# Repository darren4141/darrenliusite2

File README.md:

https://darren4141.github.io/darrenliusite2/

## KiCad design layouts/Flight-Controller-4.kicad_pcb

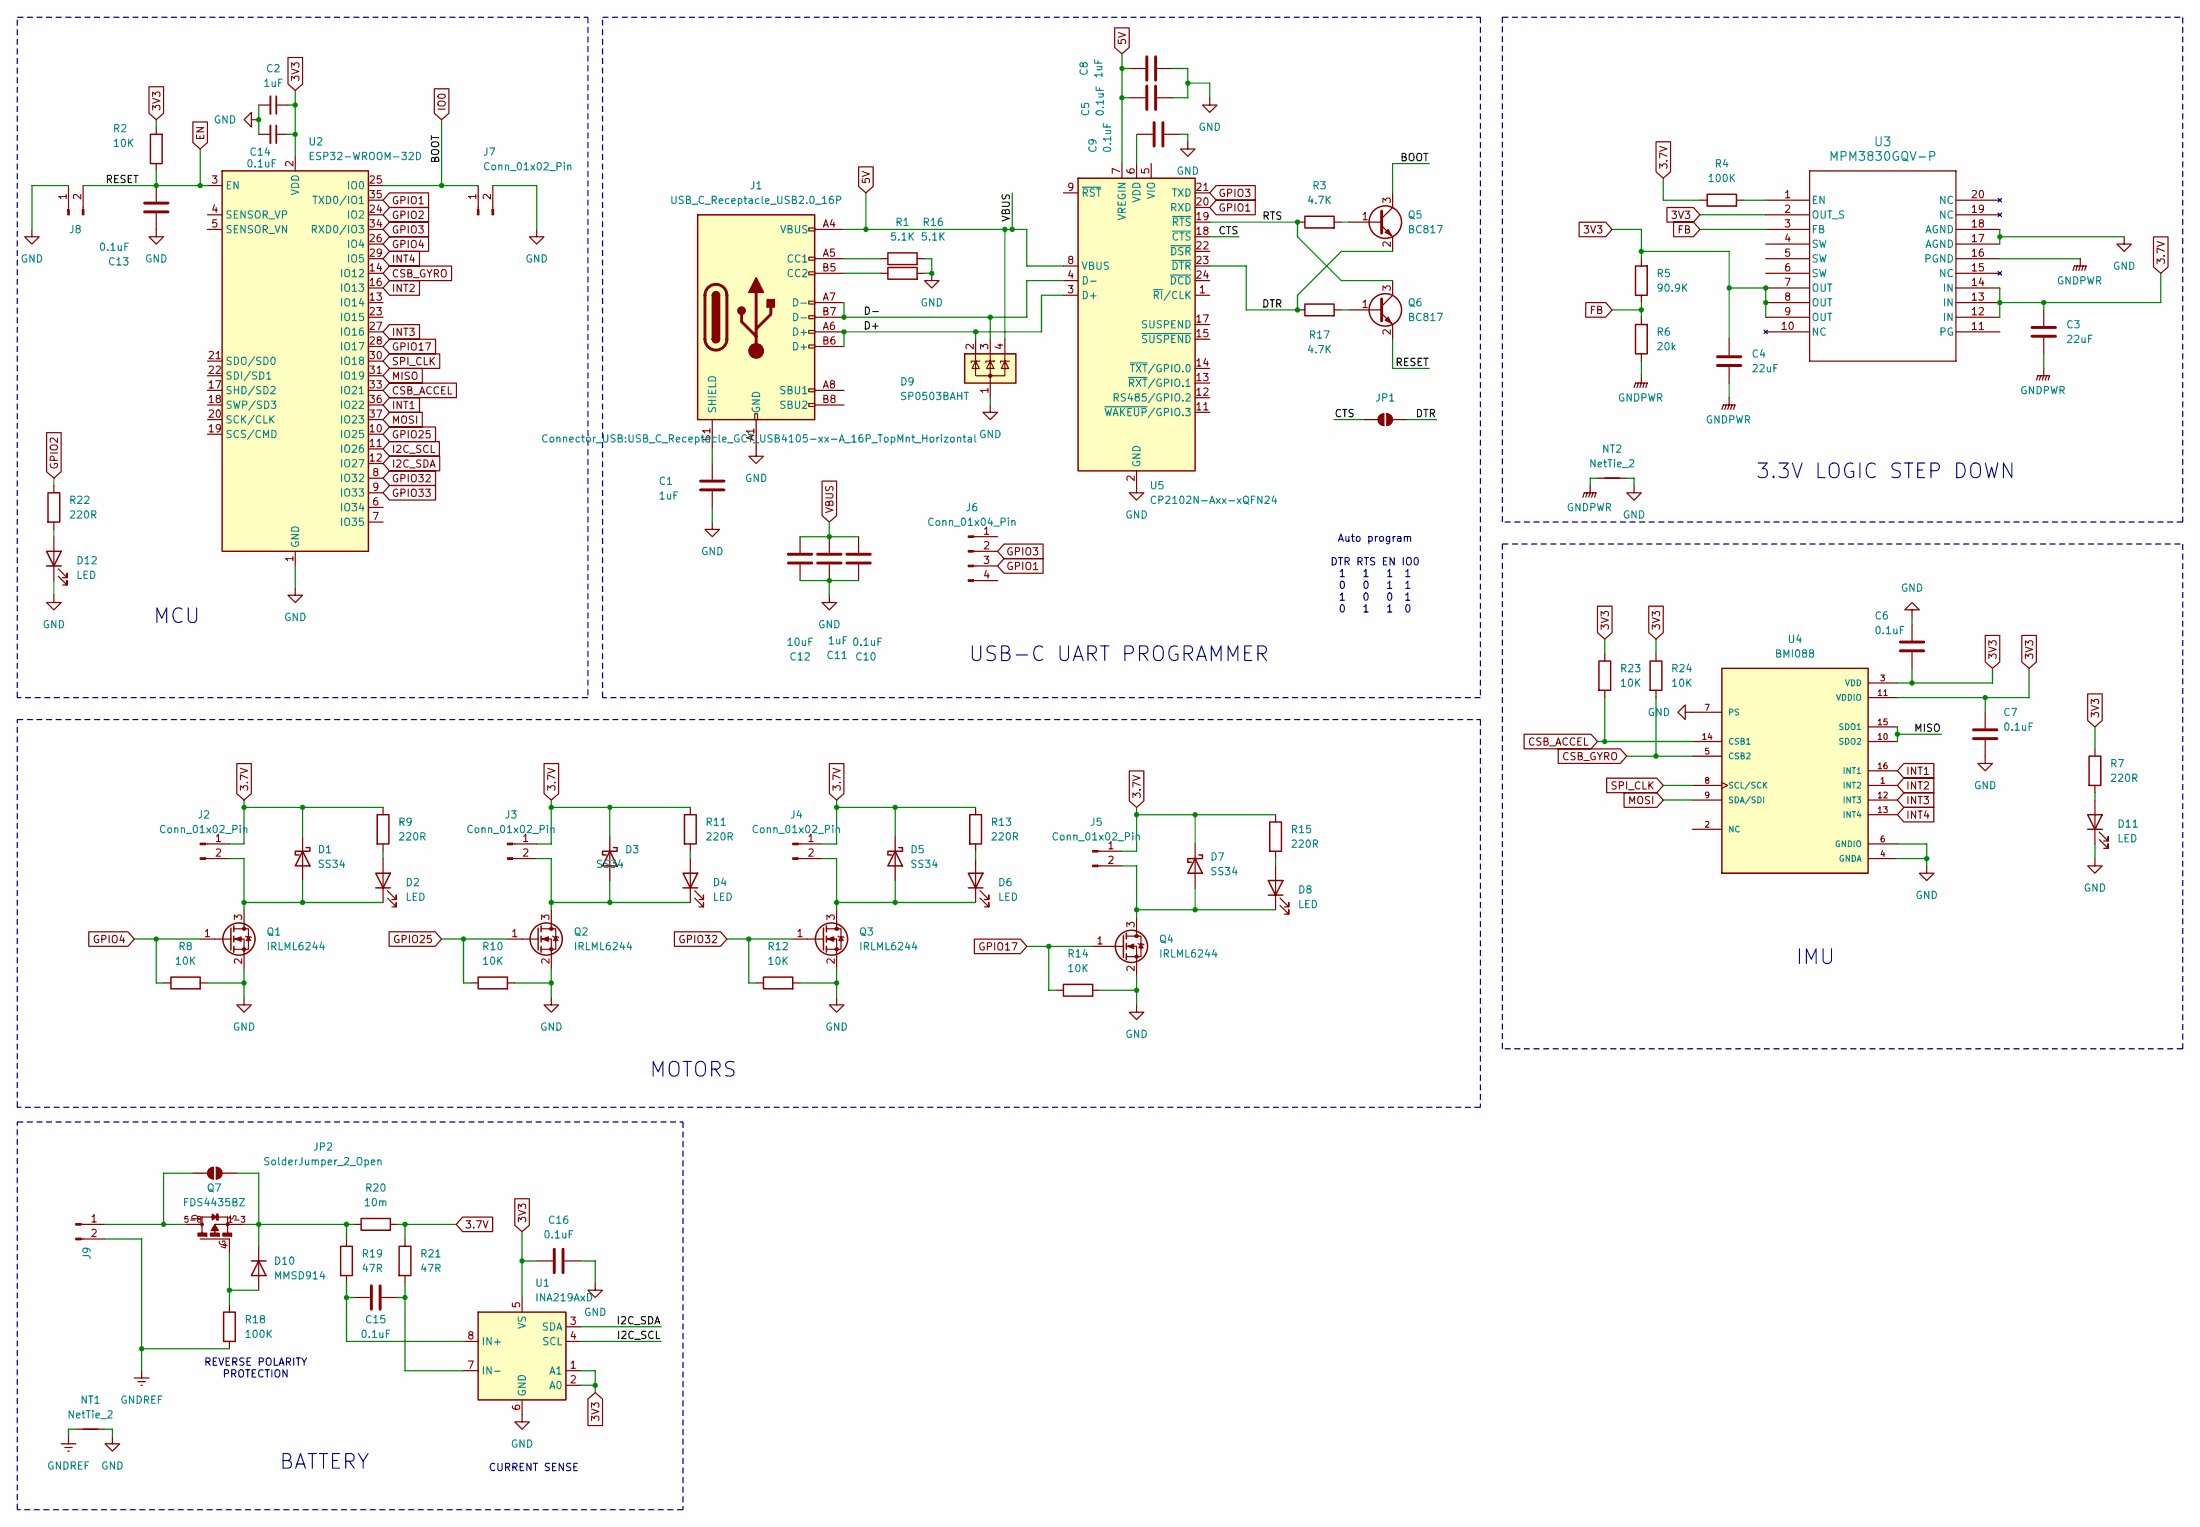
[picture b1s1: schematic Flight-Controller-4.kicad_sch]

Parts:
C1, C2, C8, C11: 1uF; C_0603_1608Metric
C3, C4: 22uF; C_1210_3225Metric
C5, C6, C7, C9, C10, C13, C14, C15, C16: 0.1uF; C_0603_1608Metric
C12: 10uF; C_0603_1608Metric
D1, D3, D5, D7: SS34; D_SMA
D2, D4, D6, D8, D11, D12: LED; LED_0603_1608Metric
D9: SP0503BAHT; SOT-143
D10: MMSD914; D_SOD-123
J1: USB_C_Receptacle_USB2.0_16P; USB_C_Receptacle_GCT_USB4105-xx-A_16P_TopMnt_Horizontal
J2, J3, J4, J5: Conn_01x02_Pin; Hirose_DF13-02P-1.25DSA_1x02_P1.25mm_Vertical
J6: Conn_01x04_Pin; PinHeader_1x04_P2.54mm_Vertical
J7, J8: Conn_01x02_Pin; PinHeader_1x02_P2.54mm_Vertical
J9: Conn_01x02_Pin; JST_XH_S2B-XH-A-1_1x02_P2.50mm_Horizontal
JP1: SolderJumper_2_Open; SolderJumper-2_P1.3mm_Open_RoundedPad1.0x1.5mm
JP2: SolderJumper_2_Open; SolderJumper-2_P1.3mm_Open_Pad1.0x1.5mm
NT1, NT2: NetTie_2; NetTie-2_SMD_Pad0.5mm
Q1, Q2, Q3, Q4: IRLML6244; SOT-23
Q5, Q6: BC817; SOT-23
Q7: FDS4435BZ; SO08-E3
R1, R16: 5.1K; R_0603_1608Metric
R2, R8, R10, R12, R14, R23, R24: 10K; R_0603_1608Metric
R3, R17: 4.7K; R_0603_1608Metric
R4, R18: 100K; R_0603_1608Metric
R5: 90.9K; R_0603_1608Metric
R6: 20k; R_0603_1608Metric
R7, R9, R11, R13, R15, R22: 220R; R_0603_1608Metric
R19, R21: 47R; R_0603_1608Metric
R20: 10m; R_0805_2012Metric
U1: INA219AxD; SOIC-8_3.9x4.9mm_P1.27mm
U2: ESP32-WROOM-32D
U3: MPM3830GQV-P; QFN3p0x5p0x1p6_MPM3830_MNP
U4: BMI088; PQFN50P450X300X100-16N
U5: CP2102N-Axx-xQFN24; QFN-24-1EP_4x4mm_P0.5mm_EP2.5x2.5mm

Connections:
3.7V: C3.1, D1.1 (K), D3.1 (K), D5.1 (K), D7.1 (K), J2.1, J3.1, J4.1, J5.1, R4.1, R9.1, R11.1, R13.1, R15.1, R20.2, R21.1, U3.12 (IN), U3.13 (IN), U3.14 (IN)
3V3: C2.1, C4.1, C6.2, C7.1, C14.1, C16.1, R2.2, R5.2, R7.1, R23.1, R24.1, U1.1 (A1), U1.2 (A0), U1.5 (VS), U2.2 (VDD), U3.2 (OUT_S), U3.7 (OUT), U3.8 (OUT), U3.9 (OUT), U4.3 (VDD), U4.11 (VDDIO)
5V: C5.1, C8.1, C10.2, C11.2, C12.2, D9.4 (K), J1.A4 (VBUS), J1.A9 (VBUS), J1.B4 (VBUS), J1.B9 (VBUS), U5.7 (VREGIN), U5.8 (VBUS)
/CTS: JP1.2 (B), U5.18 (~CTS)
/D+: D9.2 (K), J1.A6 (D+), J1.B6 (D+), U5.3 (D+)
/D-: D9.3 (K), J1.A7 (D-), J1.B7 (D-), U5.4 (D-)
/DTR: JP1.1 (A), Q5.2 (E), R17.1, U5.23 (~DTR)
/RTS: Q6.3 (C), R3.1, U5.19 (~RTS)
CSB_ACCEL: R23.2, U2.33 (IO21), U4.14 (CSB1)
CSB_GYRO: R24.2, U2.14 (IO12), U4.5 (CSB2)
EN: C13.2, J8.2, Q6.2 (E), R2.1, U2.3 (EN)
FB: R5.1, R6.2, U3.3 (FB)
GND: C1.2, C2.2, C5.2, C6.1, C7.2, C8.2, C9.2, C10.1, C11.1, C12.1, C13.1, C14.2, C16.2, D9.1 (A), D11.1 (K), D12.1 (K), J1.A1 (GND), J1.A12 (GND), J1.B1 (GND), J1.B12 (GND), J7.2, J8.1, NT1.2, NT2.2, Q1.2 (S), Q2.2 (S), Q3.2 (S), Q4.2 (S), R1.2, R8.2, R10.2, R12.2, R14.2, R16.2, U1.6 (GND), U2.1 (GND), U2.15 (GND), U2.38 (GND), U2.39 (GND), U3.17 (AGND), U3.18 (AGND), U4.4 (GNDA), U4.6 (GNDIO), U4.7 (PS), U5.2 (GND), U5.25 (GND)
GNDPWR: C3.2, C4.2, NT2.1, R6.1, U3.16 (PGND)
GNDREF: J9.2, NT1.1, R18.2
GPIO2: R22.1, U2.24 (IO2)
GPIO4: Q1.1 (G), R8.1, U2.26 (IO4)
GPIO17: Q4.1 (G), R14.1, U2.28 (IO17)
GPIO25: Q2.1 (G), R10.1, U2.10 (IO25)
GPIO32: Q3.1 (G), R12.1, U2.8 (IO32)
GPIO33: U2.9 (IO33)
I2C_SCL: U1.4 (SCL), U2.11 (IO26)
I2C_SDA: U1.3 (SDA), U2.12 (IO27)
INT1: U2.36 (IO22), U4.16 (INT1)
INT2: U2.16 (IO13), U4.1 (INT2)
INT3: U2.27 (IO16), U4.12 (INT3)
INT4: U2.29 (IO5), U4.13 (INT4)
IO0: J7.1, Q5.3 (C), U2.25 (IO0)
MISO: U2.31 (IO19), U4.10 (SDO2), U4.15 (SDO1)
MOSI: U2.37 (IO23), U4.9 (SDA/SDI)
unnamed: D1.2 (A), D2.1 (K), J2.2, Q1.3 (D)
unnamed: D2.2 (A), R9.2
unnamed: D3.2 (A), D4.1 (K), J3.2, Q2.3 (D)
unnamed: D4.2 (A), R11.2
unnamed: D5.2 (A), D6.1 (K), J4.2, Q3.3 (D)
unnamed: D6.2 (A), R13.2
unnamed: D7.2 (A), D8.1 (K), J5.2, Q4.3 (D)
unnamed: D8.2 (A), R15.2
unnamed: D10.2 (A), Q7.4, R18.1
unnamed: D10.1 (K), JP2.2 (B), Q7.1-3, R19.1, R20.1
unnamed: D11.2 (A), R7.2
unnamed: D12.2 (A), R22.2
unnamed: J1.A5 (CC1), R1.1
unnamed: J1.B5 (CC2), R16.1
unnamed: C1.1, J1.S1 (SHIELD)
unnamed: J9.1, JP2.1 (A), Q7.5-8
unnamed: Q5.1 (B), R3.2
unnamed: Q6.1 (B), R17.2
unnamed: C15.1, R19.2, U1.8 (IN+)
unnamed: C15.2, R21.2, U1.7 (IN-)
unnamed: R4.2, U3.1 (EN)
unnamed: C9.1, U5.6 (VDD)
SPI_CLK: U2.30 (IO18), U4.8 (SCL/SCK)

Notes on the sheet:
CURRENT SENSE
MOTORS
USB-C UART PROGRAMMER
MCU
REVERSE POLARITY PROTECTION
BATTERY
3.3V LOGIC STEP DOWN
Auto program DTR RTS EN IO0 1 1 1 1 0 0 1 1 1 0 0 1 0 1 1 0
IMU

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
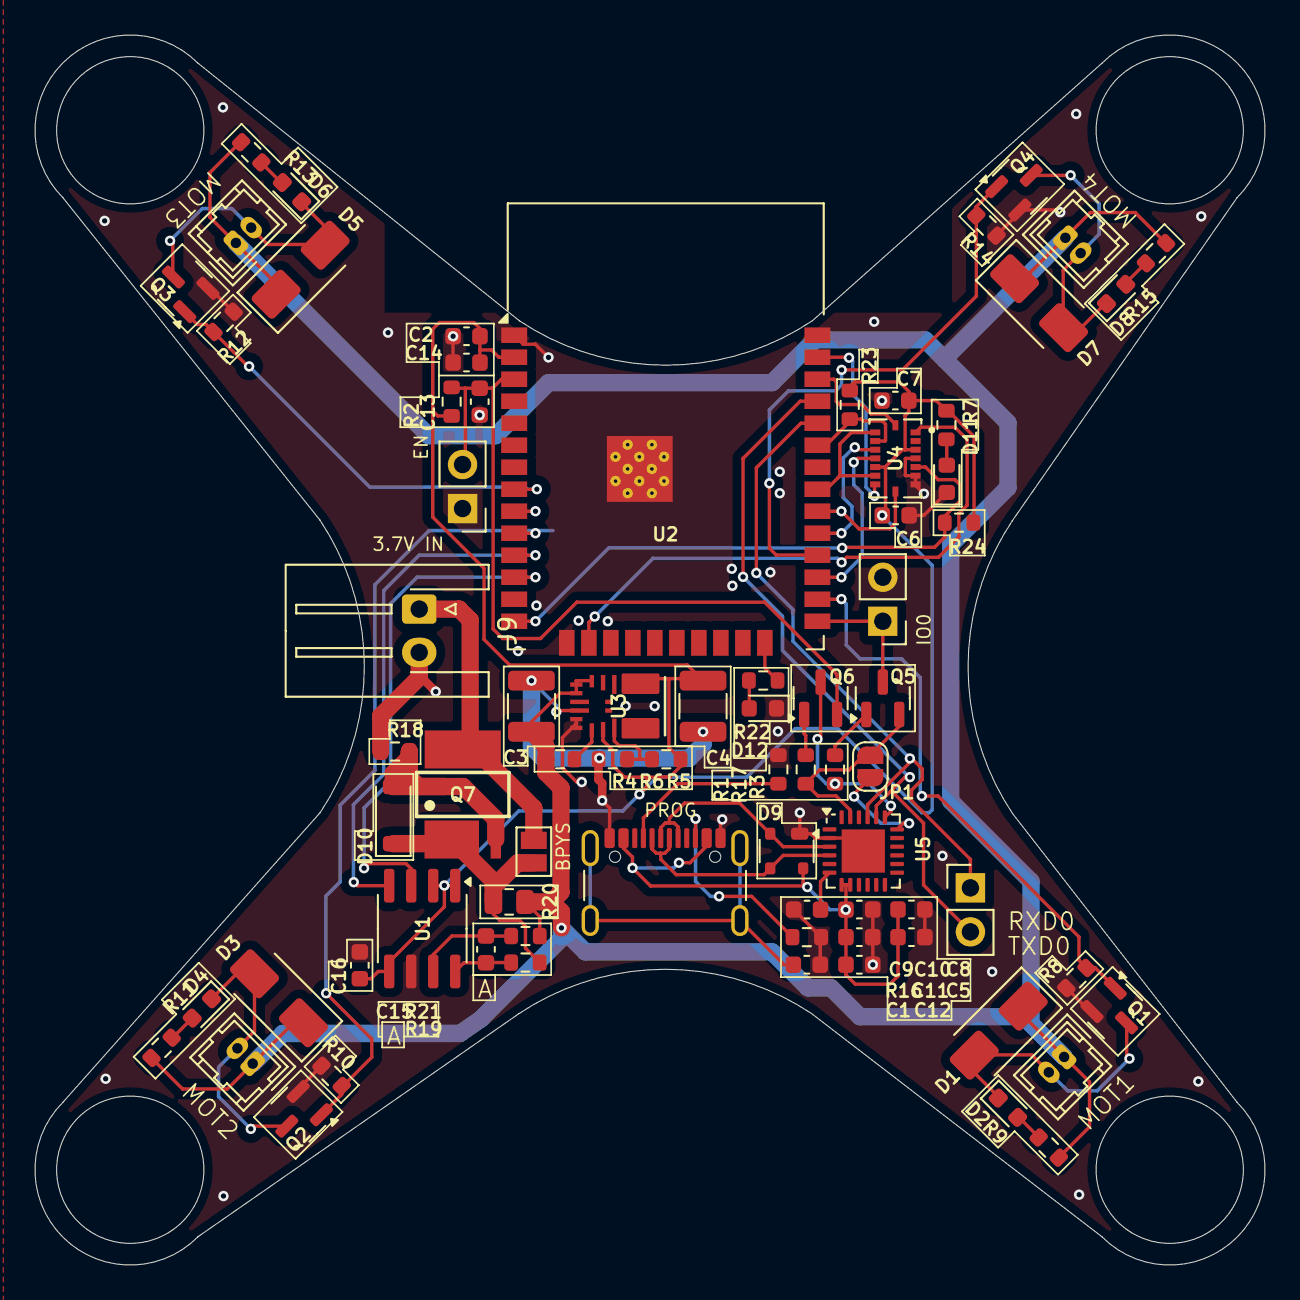
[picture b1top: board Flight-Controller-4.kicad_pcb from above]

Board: 4 copper layers, 71.0 x 71.0 mm, 77 parts (0 on the bottom side), 54 nets.

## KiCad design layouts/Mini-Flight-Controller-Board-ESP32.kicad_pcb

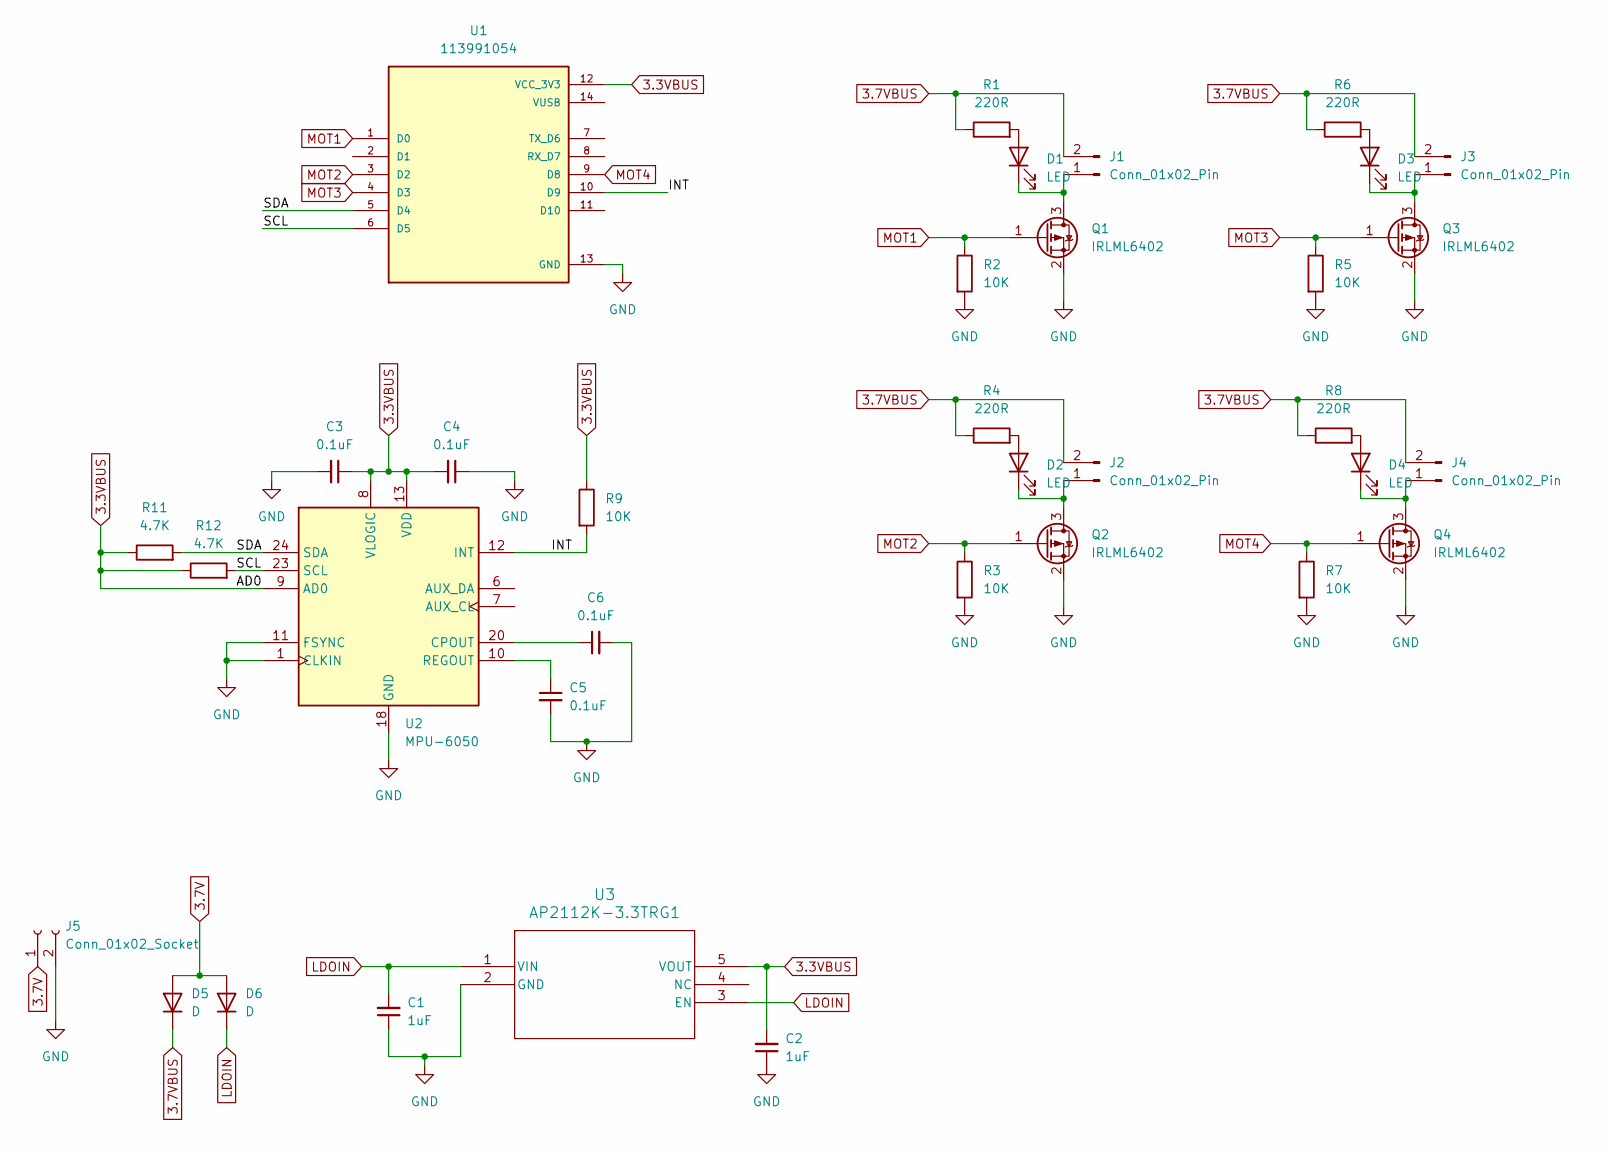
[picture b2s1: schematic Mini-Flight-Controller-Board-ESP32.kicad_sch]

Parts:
C1, C2: 1uF; C_0603_1608Metric
C3, C4, C5, C6: 0.1uF; C_0603_1608Metric
D1, D2, D3, D4: LED; LED_0603_1608Metric
D5, D6: D; D_DO-41_SOD81_P10.16mm_Horizontal
J1, J2, J3, J4: Conn_01x02_Pin; PinSocket_1x02_P1.27mm_Vertical
J5: Conn_01x02_Socket; PinHeader_1x02_P2.54mm_Vertical
Q1, Q2, Q3, Q4: IRLML6402; SOT-23
R1, R4, R6, R8: 220R; R_0603_1608Metric
R2, R3, R5, R7, R9: 10K; R_0603_1608Metric
R11, R12: 4.7K; R_0603_1608Metric
U1: 113991054; MODULE_113991054; PARTREV 23/05/2022
U2: MPU-6050; InvenSense_QFN-24_4x4mm_P0.5mm
U3: AP2112K-3.3TRG1; SOT_RG1_DIO

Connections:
3.3VBUS: C2.2, C3.1, C4.2, R9.1, R11.1, R12.1, U1.12 (VCC_3V3), U2.8 (VLOGIC), U2.9 (AD0), U2.13 (VDD), U3.5 (VOUT)
3.7V: D5.2 (A), D6.2 (A), J5.1
3.7VBUS: D5.1 (K), J1.2, J2.2, J3.2, J4.2, R1.1, R4.1, R6.1, R8.1
/INT: R9.2, U1.10 (D9), U2.12 (INT)
/SCL: R12.2, U1.6 (D5), U2.23 (SCL)
/SDA: R11.2, U1.5 (D4), U2.24 (SDA)
GND: C1.1, C2.1, C3.2, C4.1, C5.2, C6.2, J5.2, Q1.2 (S), Q2.2 (S), Q3.2 (S), Q4.2 (S), R2.2, R3.2, R5.2, R7.2, U1.13 (GND), U2.1 (CLKIN), U2.11 (FSYNC), U2.18 (GND), U3.2 (GND)
LDOIN: C1.2, D6.1 (K), U3.1 (VIN), U3.3 (EN)
MOT1: Q1.1 (G), R2.1, U1.1 (D0)
MOT2: Q2.1 (G), R3.1, U1.3 (D2)
MOT3: Q3.1 (G), R5.1, U1.4 (D3)
MOT4: Q4.1 (G), R7.1, U1.9 (D8)
unnamed: D1.2 (A), R1.2
unnamed: D1.1 (K), J1.1, Q1.3 (D)
unnamed: D2.2 (A), R4.2
unnamed: D2.1 (K), J2.1, Q2.3 (D)
unnamed: D3.2 (A), R6.2
unnamed: D3.1 (K), J3.1, Q3.3 (D)
unnamed: D4.2 (A), R8.2
unnamed: D4.1 (K), J4.1, Q4.3 (D)
unnamed: C6.1, U2.20 (CPOUT)
unnamed: C5.1, U2.10 (REGOUT)

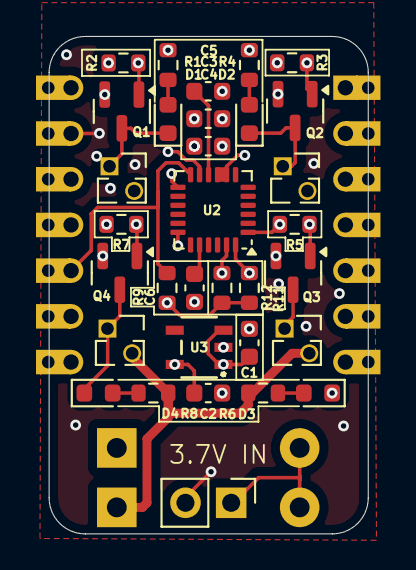
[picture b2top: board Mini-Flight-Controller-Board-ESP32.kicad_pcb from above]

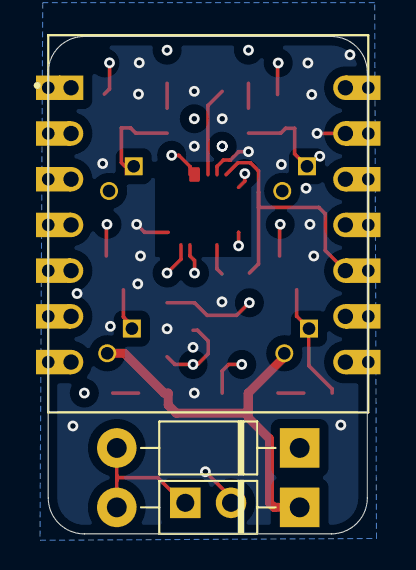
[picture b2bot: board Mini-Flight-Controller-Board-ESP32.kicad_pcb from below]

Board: 4 copper layers, 17.7 x 27.6 mm, 35 parts (3 on the bottom side), 22 nets.

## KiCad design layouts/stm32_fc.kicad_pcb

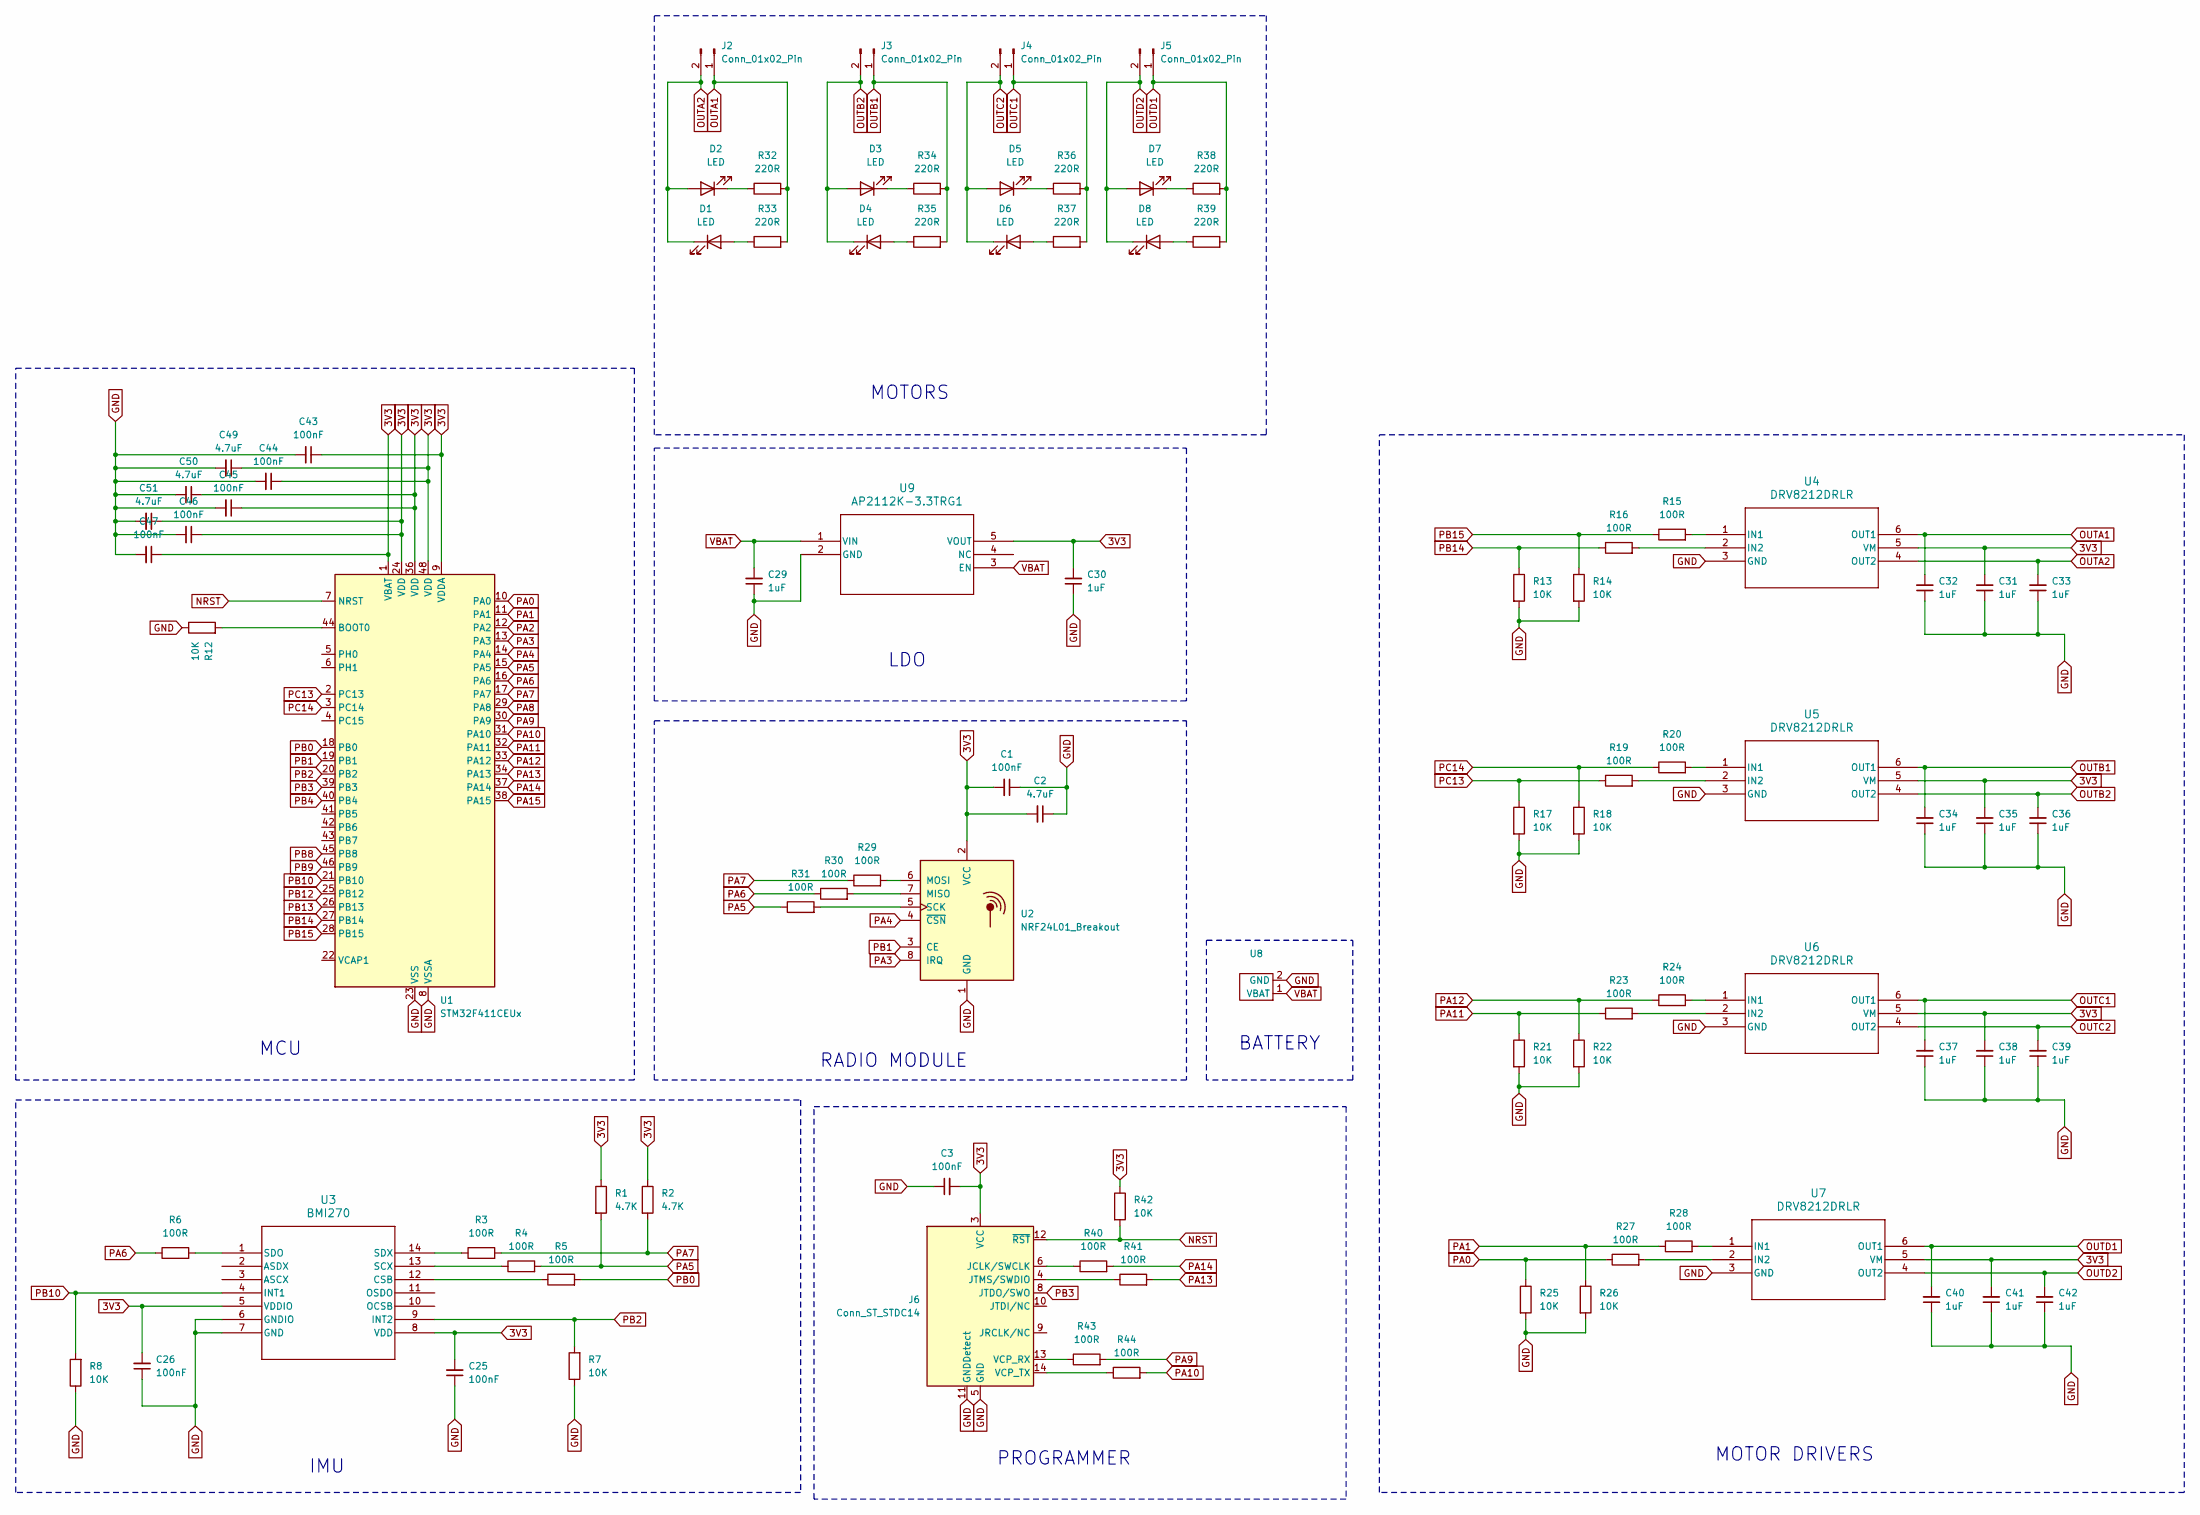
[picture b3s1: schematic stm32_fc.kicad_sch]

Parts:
C1, C3, C25, C26, C43, C44, C45, C46, C47: 100nF; C_0603_1608Metric
C2, C49, C50, C51: 4.7uF; C_0603_1608Metric
C29, C30, C31, C32, C33, C34, C35, C36, C37, C38, C39, C40, C41, C42: 1uF; C_0603_1608Metric
D1, D2, D3, D4, D5, D6, D7, D8: LED; LED_0603_1608Metric
J2, J3, J4, J5: Conn_01x02_Pin; JST_XH_B2B-XH-AM_1x02_P2.50mm_Vertical
J6: Conn_ST_STDC14; PinHeader_2x07_P1.27mm_Vertical
R1, R2: 4.7K; R_0603_1608Metric_Pad0.98x0.95mm_HandSolder
R3, R4, R5, R6, R15, R16, R19, R20, R23, R24, R27, R28, R29, R30, R31: 100R; R_0603_1608Metric_Pad0.98x0.95mm_HandSolder
R7, R8, R12, R13, R14, R17, R18, R21, R22, R25, R26, R42: 10K; R_0603_1608Metric_Pad0.98x0.95mm_HandSolder
R32, R33, R34, R35, R36, R37, R38, R39: 220R; R_0603_1608Metric
R40, R41, R43, R44: 100R; R_0603_1608Metric
U1: STM32F411CEUx; QFN-48-1EP_7x7mm_P0.5mm_EP5.6x5.6mm
U2: NRF24L01_Breakout; nRF24L01_Breakout
U3: BMI270; BMI270_BOS
U4, U5, U6, U7: DRV8212DRLR; SOT6_DRV8212_TEX
U8: Battery Connector
U9: AP2112K-3.3TRG1; SOT_RG1_DIO

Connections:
3V3: C1.2, C2.2, C3.2, C25.2, C26.2, C30.2, C31.2, C35.2, C38.2, C41.2, C43.1, C44.1, C45.1, C46.1, C47.1, C49.1, C50.1, C51.1, J6.3 (VCC), R1.1, R2.1, R42.1, U1.1 (VBAT), U1.9 (VDDA), U1.24 (VDD), U1.36 (VDD), U1.48 (VDD), U2.2 (VCC), U3.5 (VDDIO), U3.8 (VDD), U4.5 (VM), U5.5 (VM), U6.5 (VM), U7.5 (VM), U9.5 (VOUT)
GND: C1.1, C2.1, C3.1, C25.1, C26.1, C29.1, C30.1, C31.1, C32.1, C33.1, C34.1, C35.1, C36.1, C37.1, C38.1, C39.1, C40.1, C41.1, C42.1, C43.2, C44.2, C45.2, C46.2, C47.2, C49.2, C50.2, C51.2, J6.5 (GND), J6.7 (GND), J6.11 (GNDDetect), R7.1, R8.1, R12.1, R13.2, R14.2, R17.2, R18.2, R21.2, R22.2, R25.2, R26.2, U1.8 (VSSA), U1.23 (VSS), U1.35 (VSS), U1.47 (VSS), U1.49 (VSS), U2.1 (GND), U3.6 (GNDIO), U3.7 (GND), U4.3 (GND), U5.3 (GND), U6.3 (GND), U7.3 (GND), U8.2 (GND), U9.2 (GND)
NRST: J6.12 (~RST), R42.2, U1.7 (NRST)
unnamed: D1.2 (A), R33.1
unnamed: D2.1 (K), R32.1
unnamed: D3.1 (K), R34.1
unnamed: D4.2 (A), R35.1
unnamed: D5.1 (K), R36.1
unnamed: D6.2 (A), R37.1
unnamed: D7.1 (K), R38.1
unnamed: D8.2 (A), R39.1
unnamed: J6.6 (JCLK/SWCLK), R40.1
unnamed: J6.4 (JTMS/SWDIO), R41.1
unnamed: J6.13 (VCP_RX), R43.1
unnamed: J6.14 (VCP_TX), R44.1
unnamed: R12.2, U1.44 (BOOT0)
unnamed: R30.2, U2.7 (MISO)
unnamed: R29.2, U2.6 (MOSI)
unnamed: R31.2, U2.5 (SCK)
unnamed: R5.1, U3.12 (CSB)
unnamed: R4.1, U3.13 (SCX)
unnamed: R6.2, U3.1 (SDO)
unnamed: R3.1, U3.14 (SDX)
unnamed: R15.2, U4.1 (IN1)
unnamed: R16.2, U4.2 (IN2)
unnamed: R20.2, U5.1 (IN1)
unnamed: R19.2, U5.2 (IN2)
unnamed: R24.2, U6.1 (IN1)
unnamed: R23.2, U6.2 (IN2)
unnamed: R28.2, U7.1 (IN1)
unnamed: R27.2, U7.2 (IN2)
OUTA1: C32.2, J2.1, R32.2, R33.2, U4.6 (OUT1)
OUTA2: C33.2, D1.1 (K), D2.2 (A), J2.2, U4.4 (OUT2)
OUTB1: C34.2, J3.1, R34.2, R35.2, U5.6 (OUT1)
OUTB2: C36.2, D3.2 (A), D4.1 (K), J3.2, U5.4 (OUT2)
OUTC1: C37.2, J4.1, R36.2, R37.2, U6.6 (OUT1)
OUTC2: C39.2, D5.2 (A), D6.1 (K), J4.2, U6.4 (OUT2)
OUTD1: C40.2, J5.1, R38.2, R39.2, U7.6 (OUT1)
OUTD2: C42.2, D7.2 (A), D8.1 (K), J5.2, U7.4 (OUT2)
PA0: R25.1, R27.1, U1.10 (PA0)
PA1: R26.1, R28.1, U1.11 (PA1)
PA2: U1.12 (PA2)
PA3: U1.13 (PA3), U2.8 (IRQ)
PA4: U1.14 (PA4), U2.4 (~CSN)
PA5: R1.2, R4.2, R31.1, U1.15 (PA5)
PA6: R6.1, R30.1, U1.16 (PA6)
PA7: R2.2, R3.2, R29.1, U1.17 (PA7)
PA8: U1.29 (PA8)
PA9: R43.2, U1.30 (PA9)
PA10: R44.2, U1.31 (PA10)
PA11: R21.1, R23.1, U1.32 (PA11)
PA12: R22.1, R24.1, U1.33 (PA12)
PA13: R41.2, U1.34 (PA13)
PA14: R40.2, U1.37 (PA14)
PA15: U1.38 (PA15)
PB0: R5.2, U1.18 (PB0)
PB1: U1.19 (PB1), U2.3 (CE)
PB2: R7.2, U1.20 (PB2), U3.9 (INT2)
PB3: J6.8 (JTDO/SWO), U1.39 (PB3)
PB4: U1.40 (PB4)
PB8: U1.45 (PB8)
PB9: U1.46 (PB9)
PB10: R8.2, U1.21 (PB10), U3.4 (INT1)
PB12: U1.25 (PB12)
PB13: U1.26 (PB13)
PB14: R13.1, R16.1, U1.27 (PB14)
PB15: R14.1, R15.1, U1.28 (PB15)
PC13: R17.1, R19.1, U1.2 (PC13)
PC14: R18.1, R20.1, U1.3 (PC14)
VBAT: C29.2, U8.1 (VBAT), U9.1 (VIN), U9.3 (EN)

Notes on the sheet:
MOTORS
IMU
MOTOR DRIVERS
LDO
RADIO MODULE
MCU
BATTERY
PROGRAMMER

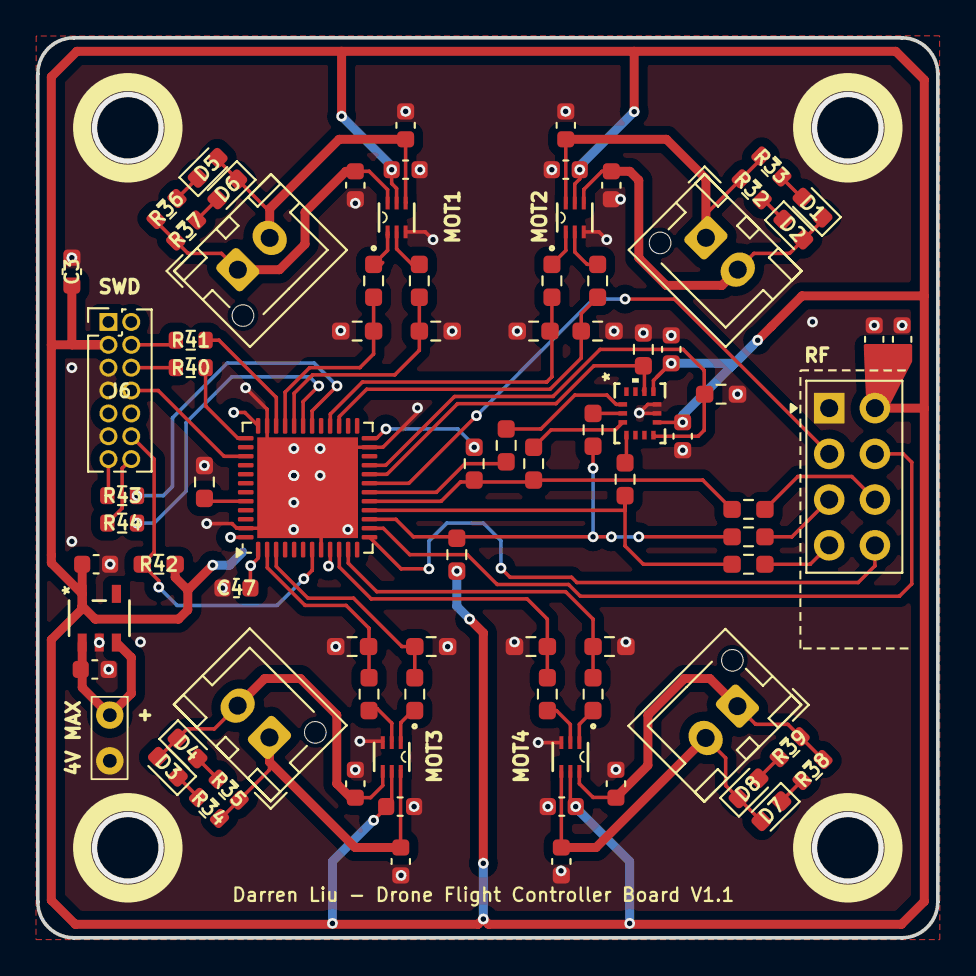
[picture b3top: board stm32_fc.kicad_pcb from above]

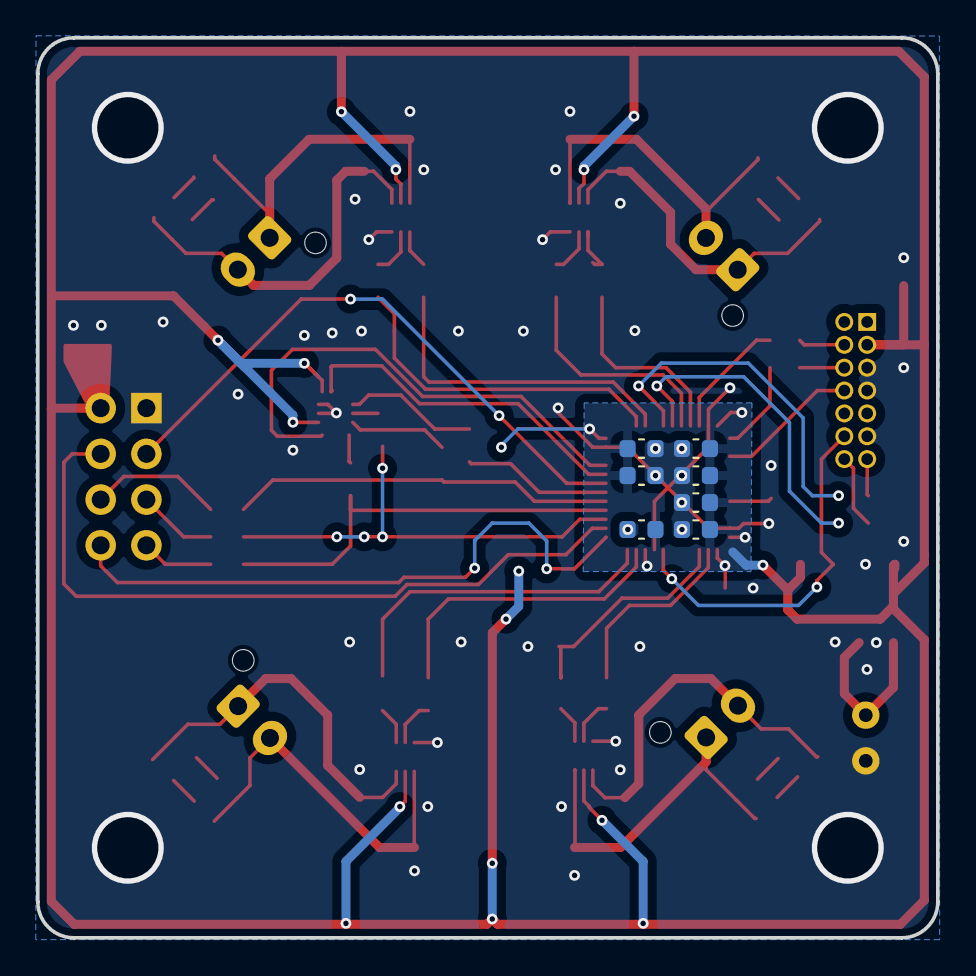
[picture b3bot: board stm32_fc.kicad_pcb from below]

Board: 2 copper layers, 50.0 x 50.0 mm, 90 parts (7 on the bottom side), 62 nets.

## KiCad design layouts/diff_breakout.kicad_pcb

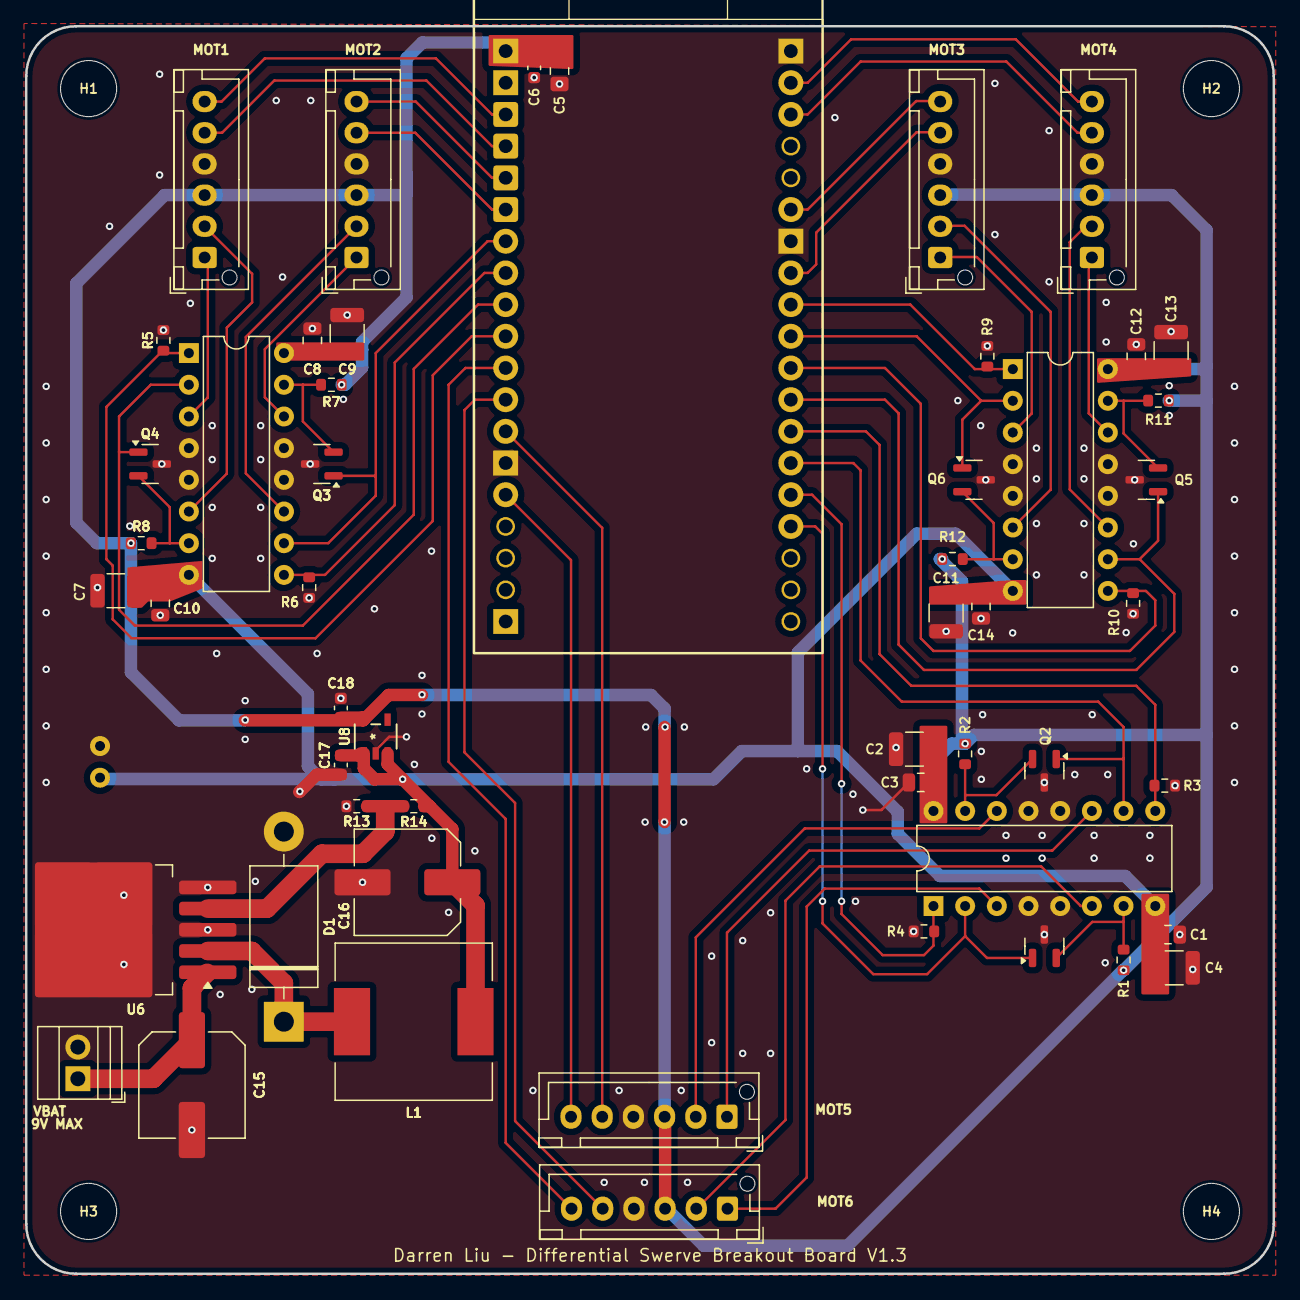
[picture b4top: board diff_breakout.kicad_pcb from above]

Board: 2 copper layers, 100.0 x 100.0 mm, 57 parts (0 on the bottom side), 48 nets.

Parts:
C1, C3, C8, C10, C12, C14: 100nF; C_0805_2012Metric
C2, C9, C13: 1uF; C_1210_3225Metric
C4, C7, C11: 10uF; C_1210_3225Metric
C5: C_Small; C_0805_2012Metric_Pad1.18x1.45mm_HandSolder
C6: C_Small; C_0603_1608Metric
C15: 470uF; C_Elec_8x10.2
C16: 220uF; C_Elec_8x10.2
C17, C18: 1uF; C_0603_1608Metric
D1: 1N5822; D_DO-201AD_P15.24mm_Horizontal
H1, H2, H3, H4: MountingHole; MountingHole_4.5mm
J1, J2, J3, J4, J5, J6: Conn_01x06_Pin; JST_XH_B6B-XH-AM_1x06_P2.50mm_Vertical
J7: Screw_Terminal_01x02; TerminalBlock_Xinya_XY308-2.54-2P_1x02_P2.54mm_Horizontal
L1: 68uH; L_12x12mm_H6mm
Q1, Q2, Q3, Q4, Q5, Q6: BSS138; SOT-23
R1, R2, R3, R4, R5, R6, R7, R8, R9, R10, R11, R12: 10K; R_0603_1608Metric
R13: 1K; R_0603_1608Metric
R14: 3.9K; R_0603_1608Metric
U3, U4, U7: L293D; DIP-16_W7.62mm
U5: ESP32-WROOM-38
U6: LM2596S-3.3; TO-263-5_TabPin3
U8: AP2112K-3.3TRG1; SOT_RG1_DIO

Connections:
3V3: C2.2, C3.1, C5.2, C6.2, C8.1, C9.2, C12.1, C13.2, C18.2, J1.3, J2.3, J3.3, J4.3, J5.3, J6.3, R1.2, R2.1, R7.1, R8.2, R11.1, R12.2, U3.16 (VCC1), U4.16 (VCC1), U5.2 (3V3), U7.16 (VCC1), U8.5 (VOUT)
6V: C1.2, C4.1, C7.1, C10.2, C11.1, C14.2, C16.1, C17.2, L1.2, R14.2, U3.8 (VCC2), U4.8 (VCC2), U7.8 (VCC2), U8.1 (VIN), U8.3 (EN)
9V: C15.1, J7.1, U6.1 (VIN)
GND: C1.1, C2.1, C3.2, C4.2, C5.1, C6.1, C7.2, C8.2, C9.1, C10.1, C11.2, C12.2, C13.1, C14.1, C15.2, C16.2, C17.1, C18.1, D1.2 (A), J1.4, J2.4, J3.4, J4.4, J5.4, J6.4, J7.2, Q1.3 (D), Q2.3 (D), Q3.3 (D), Q4.3 (D), Q5.3 (D), Q6.3 (D), R3.2, R4.1, R5.1, R6.2, R9.1, R10.2, R13.1, U3.4 (GND), U3.5 (GND), U3.12 (GND), U3.13 (GND), U4.4 (GND), U4.5 (GND), U4.12 (GND), U4.13 (GND), U5.1 (GND), U5.32 (GND), U5.38 (GND), U6.3 (GND), U6.5 (~ON/OFF), U7.4 (GND), U7.5 (GND), U7.12 (GND), U7.13 (GND), U8.2 (GND)
GPIO0: Q2.1 (G), U5.25 (GPIO0), U7.10 (3A)
GPIO2: R4.2, U5.24 (GPIO2), U7.1 (EN1,2)
GPIO4: R3.1, U5.26 (GPIO4), U7.9 (EN3,4)
GPIO5: Q6.1 (G), U4.2 (1A), U5.29 (GPIO5)
GPIO12: J6.5, U5.14 (GPIO12)
GPIO13: J6.6, U5.16 (GPIO13)
GPIO14: J5.5, U5.13 (GPIO14)
GPIO15: Q1.1 (G), U5.23 (GPIO15), U7.2 (1A)
GPIO16: Q5.1 (G), U4.10 (3A), U5.27 (GPIO16)
GPIO17: R10.1, U4.9 (EN3,4), U5.28 (GPIO17)
GPIO18: R9.2, U4.1 (EN1,2), U5.30 (GPIO18)
GPIO19: J3.5, U5.31 (GPIO19)
GPIO21: J3.6, U5.33 (GPIO21)
GPIO22: J4.5, U5.36 (GPIO22)
GPIO23: J4.6, U5.37 (GPIO23)
GPIO25: Q4.1 (G), U3.2 (1A), U5.10 (GPIO25)
GPIO26: R5.2, U3.1 (EN1,2), U5.11 (GPIO26)
GPIO27: J5.6, U5.12 (GPIO27)
GPIO32: Q3.1 (G), U3.10 (3A), U5.8 (GPIO32)
GPIO33: R6.1, U3.9 (EN3,4), U5.9 (GPIO33)
GPIO34: J2.6, U5.6 (GPIO34)
GPIO35: J2.5, U5.7 (GPIO35)
GPIO36: J1.6, U5.4 (GPIO36)
GPIO39: J1.5, U5.5 (GPIO39)
MA+: J1.1, U3.3 (1Y)
MA-: J1.2, U3.6 (2Y)
MB+: J2.1, U3.14 (4Y)
MB-: J2.2, U3.11 (3Y)
MC+: J3.1, U4.3 (1Y)
MC-: J3.2, U4.6 (2Y)
MD+: J4.1, U4.14 (4Y)
MD-: J4.2, U4.11 (3Y)
ME+: J5.1, U7.3 (1Y)
ME-: J5.2, U7.6 (2Y)
MF+: J6.1, U7.11 (3Y)
MF-: J6.2, U7.14 (4Y)
unnamed: D1.1 (K), L1.1, U6.2 (OUT)
unnamed: Q1.2 (S), R1.1, U7.7 (2A)
unnamed: Q2.2 (S), R2.2, U7.15 (4A)
unnamed: Q3.2 (S), R7.2, U3.15 (4A)
unnamed: Q4.2 (S), R8.1, U3.7 (2A)
unnamed: Q5.2 (S), R11.2, U4.15 (4A)
unnamed: Q6.2 (S), R12.1, U4.7 (2A)
unnamed: R13.2, R14.1, U6.4 (FB)
